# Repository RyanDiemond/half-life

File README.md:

# HalfLife-Week1:
<h1> This is my Starbie project for Hack club Half Life. It is a motion controlled digital physical desk pet. </h1>
<h3> Starbie is a motion-controlled digital desk pet with a climate sensor, motion sensor, screen, and two buttons for input which will be programmed on the Arduino IDE.</h3>

This is my schematic; I have a XIAO ESP32 C3 board, two buttons, dht11 sensor, display screen, mpu6050, and a resistor. The schematic also shows how all the wiring is connected.

This is my base PCB; it is in a star shape. Within my PCB I used wires for all the power connections and I used a fill layer for the GND.

This is my personalized PCB; It has words on it that says "Made by Ryan" and it has two pictures of a cheetah running.

# BOM:
This is my BOM and it gives how much everything is plus shipping and tax.

| Part | Cost (total) | Need |
| :--- | :--- | :--- |
| XIAO ESP32 C3 | $4.99 | The microcontroller (how all actions and decisons are made) |
| DHT11 | $3.78 | climate sensor |
| Resistor | $3.99 | Controls how much power goes through the board at a time |
| buttons | $5.99 | Allows for inputs |
| Display screen | $4.99 | Displays inputs and outputs |
| MPU6050 | $2.19 | Detects movement |
| PCB | $8.70 | The main board that makes all connections |
|Tax and shipping|$32.61||
||$67.24||

I am using tier two for this project because of how much the tax and shipping is.

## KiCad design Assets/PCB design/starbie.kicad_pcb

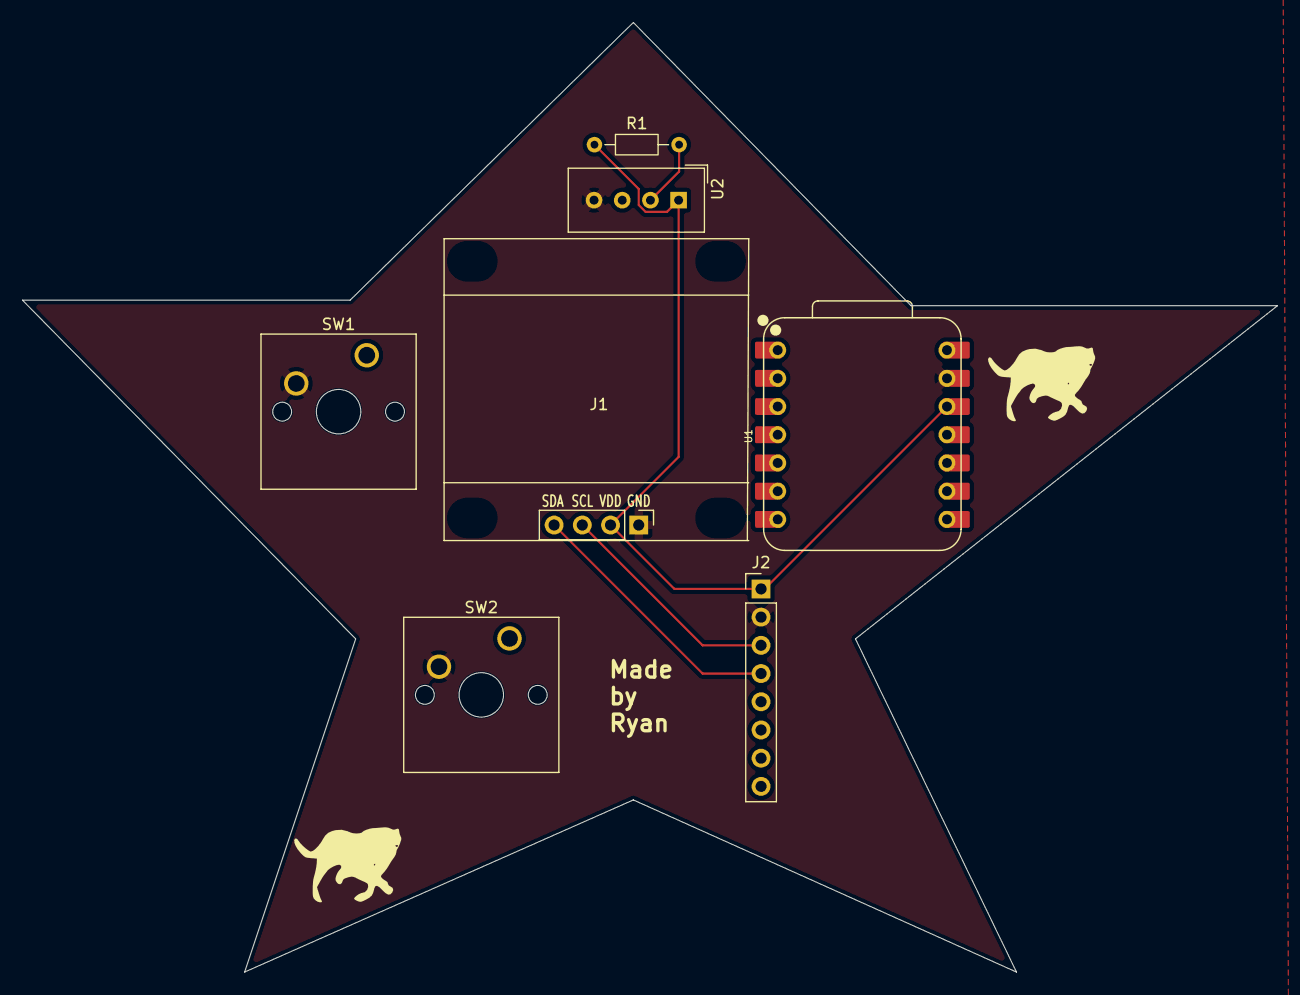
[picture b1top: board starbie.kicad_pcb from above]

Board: 2 copper layers, 113.0 x 85.5 mm, 7 parts (0 on the bottom side), 5 nets.

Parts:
J1: Conn_01x04_Pin; Display_128x64_096_I2C
J2: Conn_01x08_Pin; PinHeader_1x08_P2.54mm_Vertical
R1: 10k; R_Axial_DIN0204_L3.6mm_D1.6mm_P7.62mm_Horizontal
SW1, SW2: SW_Push; SW_Cherry_MX_1.00u_PCB
U1: XIAO-ESP32-C3-SMD; XIAO-ESP32-C6-DIP
U2: DHT11; Aosong_DHT11_5.5x12.0_P2.54mm

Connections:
+3.3V: J1.2, J2.1, R1.1, U1.12 (3V3_OUT), U2.1 (VDD)
/DHT11 DATA: R1.2, U2.2 (DATA)
/SCL: J1.3, J2.3
/SDA: J1.4, J2.4
GND: J1.1, J2.2, SW1.2, SW2.2, U1.13 (GND), U2.4 (GND)
